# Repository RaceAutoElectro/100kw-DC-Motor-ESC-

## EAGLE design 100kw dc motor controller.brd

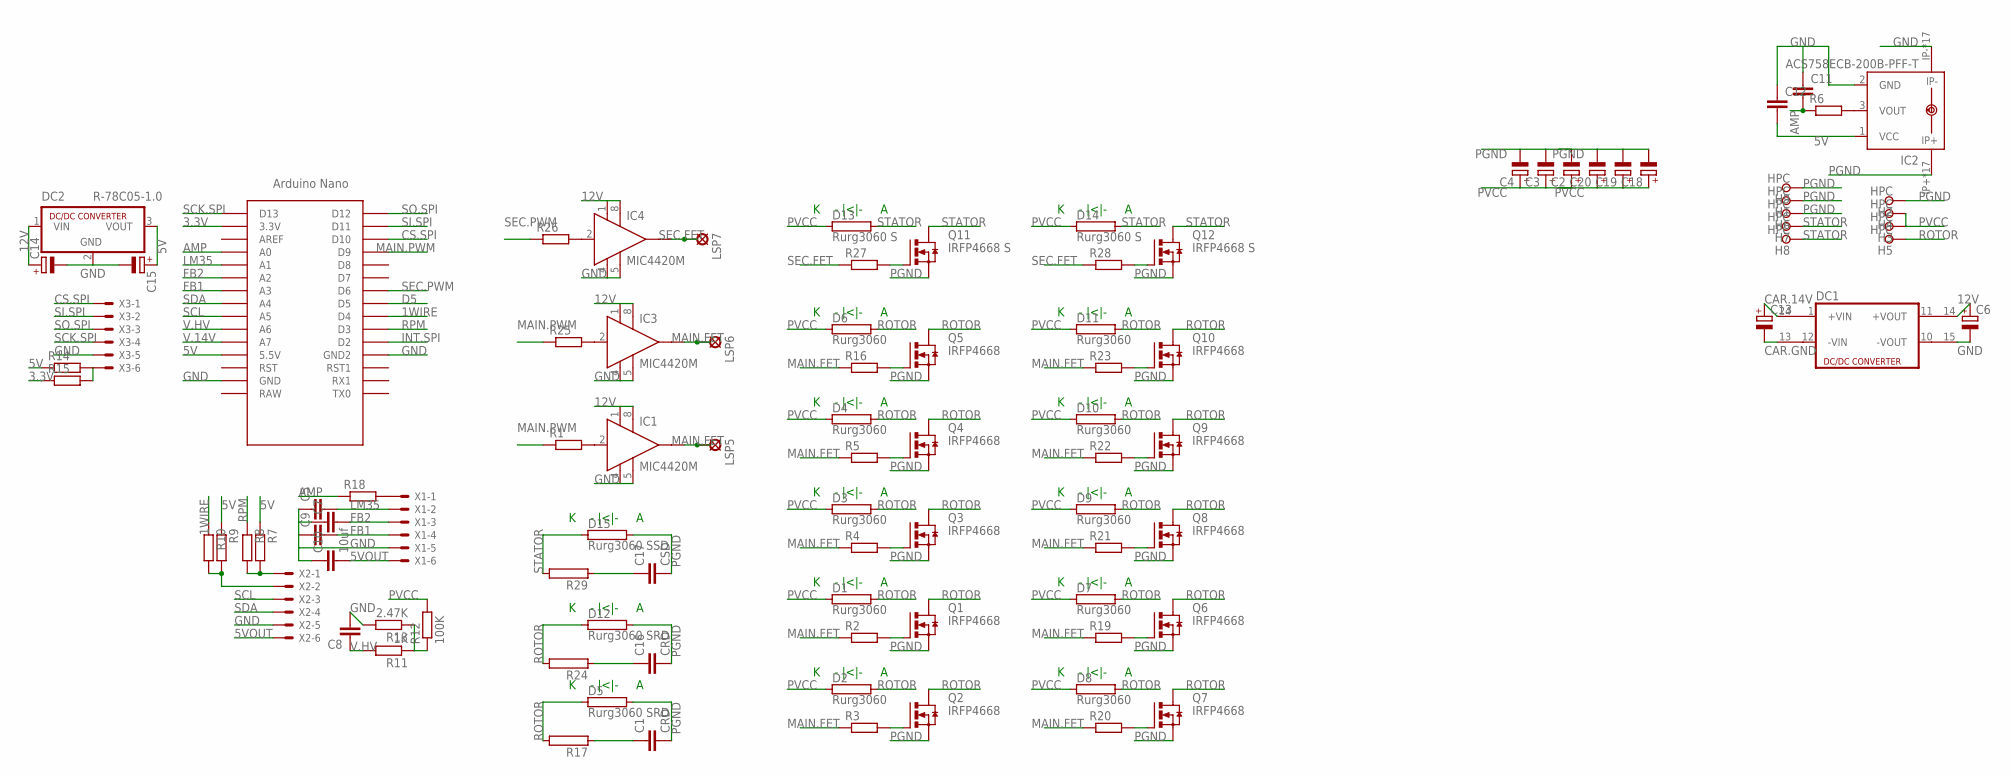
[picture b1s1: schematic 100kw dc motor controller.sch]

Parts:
C1, C16: CRD; C37.5B20
C2, C3, C4, C18, C19, C20: CPOL-EUE10-35; EB35D
C5, C7, C8, C9, C11, C12: C-EUC1206; C1206
C6, C13: CPOL-EUE3.5-10; E3,5-10
C10: 10uf; C1812
C14, C15: CPOL-EUD/7343-31W; D/7343-31W
C17: CSD; C37.5B20
D1, D2, D3, D4, D6, D7, D8, D9, D10, D11: Rurg3060; TO-247-2H
D5, D12: Rurg3060 SRD; TO-247-2V
D13, D14: Rurg3060 S; TO-247-2H
D15: Rurg3060 SSD; TO-247-2V
DC1: DCW1U; DCW
DC2: R-78C05-1.0; SIP3
H1, H2, H3, H4, H5, H6, H7, H8, H9: HPC; PAD_0.2500
IC1, IC3, IC4: MIC4420M; SO-08
IC2: ACS758ECB-200B-PFF-T; CB-PFF
LSP5, LSP6, LSP7: LSP11
Q1, Q2, Q3, Q4, Q5, Q6, Q7, Q8, Q9, Q10: IRFP4668; TO247BH
Q11, Q12: IRFP4668 S; TO247BH
R1, R6, R7, R8, R9, R10, R14, R15, R18, R25, R26: R-EU_R1206; R1206
R2, R3, R4, R5, R16, R19, R20, R21, R22, R23, R27, R28: R-EU_M5923; M5923
R11: 1K; R1206
R12: 100K; R1206
R13: 2.47K; R1206
R17, R24, R29: RKH208-8R; KH208R-8
U$1: NANO
X1, X2, X3: 22-23-2061

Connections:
1WIRE: R10.1, U$1.D4
3.3V: R15.1, U$1.3.3V
5V: C12.2, C15.+, DC2.3 (VOUT), IC2.1 (VCC), R7.1, R9.1, R14.1, U$1.5V (5.5V)
5VOUT: C10.2, X1.6, X2.6
12V: C6.+, C14.+, DC1.14 (+VOUT1), DC2.1 (VIN), IC1.1 (VS), IC1.8 (VS1), IC3.1 (VS), IC3.8 (VS1), IC4.1 (VS), IC4.8 (VS1)
AMP: C11.2, R6.1, R18.1, U$1.A0
CAR.14V: C13.+, DC1.24 (+VIN1)
CAR.GND: C13.-, DC1.13 (-VIN1)
CS.SPI: U$1.D10, X3.1
D5: U$1.D5
FB1: C9.2, U$1.A3, X1.4
FB2: C7.2, U$1.A2, X1.3
GND: C5.1, C6.-, C7.1, C8.2, C9.1, C10.1, C11.1, C12.1, C14.-, C15.-, DC1.15 (-VOUT1), DC2.2 (GND), IC1.4 (GND), IC1.5 (GND1), IC2.2 (GND), IC2.IP-, IC2.IP-@2 (IP-), IC2.IP-@3 (IP-), IC2.IP-@4 (IP-), IC2.IP-@5 (IP-), IC2.IP-@6 (IP-), IC2.IP-@7 (IP-), IC2.IP-@8 (IP-), IC2.IP-@9 (IP-), IC2.IP-@10 (IP-), IC2.IP-@11 (IP-), IC2.IP-@12 (IP-), IC2.IP-@13 (IP-), IC2.IP-@14 (IP-), IC2.IP-@15 (IP-), IC2.IP-@16 (IP-), IC2.IP-@17 (IP-), IC3.4 (GND), IC3.5 (GND1), IC4.4 (GND), IC4.5 (GND1), R13.2, U$1.GND, U$1.GND1 (GND2), X1.5, X2.5, X3.5
INT.SPI: U$1.D2
LM35: C5.2, U$1.A1, X1.2
MAIN.FET: IC1.6 (OUT), IC3.6 (OUT), LSP5.MP, LSP6.MP, R2.1, R3.1, R4.1, R5.1, R16.1, R19.1, R20.1, R21.1, R22.1, R23.1
MAIN.PWM: R1.1, R25.1, U$1.D9
unnamed: IC1.2 (IN), R1.2
unnamed: Q1.G, R2.2
unnamed: Q2.G, R3.2
unnamed: Q3.G, R4.2
unnamed: Q4.G, R5.2
unnamed: IC2.3 (VOUT), R6.2
unnamed: R9.2, R10.2, X2.2
unnamed: R7.2, R8.2, X2.1
unnamed: R14.2, R15.2, X3.6
unnamed: Q5.G, R16.2
unnamed: C1.1, R17.1
unnamed: R18.2, X1.1
unnamed: R11.1, R12.1, R13.1
unnamed: Q6.G, R19.2
unnamed: Q7.G, R20.2
unnamed: Q8.G, R21.2
unnamed: Q9.G, R22.2
unnamed: Q10.G, R23.2
unnamed: C16.1, R24.1
unnamed: IC3.2 (IN), R25.2
unnamed: IC4.2 (IN), R26.2
unnamed: Q11.G, R27.2
unnamed: Q12.G, R28.2
unnamed: C17.1, R29.1
PGND: C1.2, C2.-, C3.-, C4.-, C16.2, C17.2, C18.-, C19.-, C20.-, D5.2, D12.2, D15.2, H1.1, H2.1, H6.1, H9.1, IC2.IP+, IC2.IP+@2 (IP+), IC2.IP+@3 (IP+), IC2.IP+@4 (IP+), IC2.IP+@5 (IP+), IC2.IP+@6 (IP+), IC2.IP+@7 (IP+), IC2.IP+@8 (IP+), IC2.IP+@9 (IP+), IC2.IP+@10 (IP+), IC2.IP+@11 (IP+), IC2.IP+@12 (IP+), IC2.IP+@13 (IP+), IC2.IP+@14 (IP+), IC2.IP+@15 (IP+), IC2.IP+@16 (IP+), IC2.IP+@17 (IP+), Q1.S, Q2.S, Q3.S, Q4.S, Q5.S, Q6.S, Q7.S, Q8.S, Q9.S, Q10.S, Q11.S, Q12.S
PVCC: C2.+, C3.+, C4.+, C18.+, C19.+, C20.+, D1.1, D2.1, D3.1, D4.1, D6.1, D7.1, D8.1, D9.1, D10.1, D11.1, D13.1, D14.1, H3.1, H4.1, R12.2
ROTOR: D1.2, D2.2, D3.2, D4.2, D5.1, D6.2, D7.2, D8.2, D9.2, D10.2, D11.2, D12.1, H5.1, Q1.D, Q2.D, Q3.D, Q4.D, Q5.D, Q6.D, Q7.D, Q8.D, Q9.D, Q10.D, R17.2, R24.2
RPM: R8.1, U$1.D3
SCK.SPI: U$1.D13, X3.4
SCL: U$1.A5, X2.3
SDA: U$1.A4, X2.4
SEC.FET: IC4.6 (OUT), LSP7.MP, R27.1, R28.1
SEC.PWM: R26.1, U$1.D6
SI.SPI: U$1.D11, X3.2
SO.SPI: U$1.D12, X3.3
STATOR: D13.2, D14.2, D15.1, H7.1, H8.1, Q11.D, Q12.D, R29.2
V.14V: U$1.A7
V.HV: C8.1, R11.2, U$1.A6

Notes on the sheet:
K - |<|- A

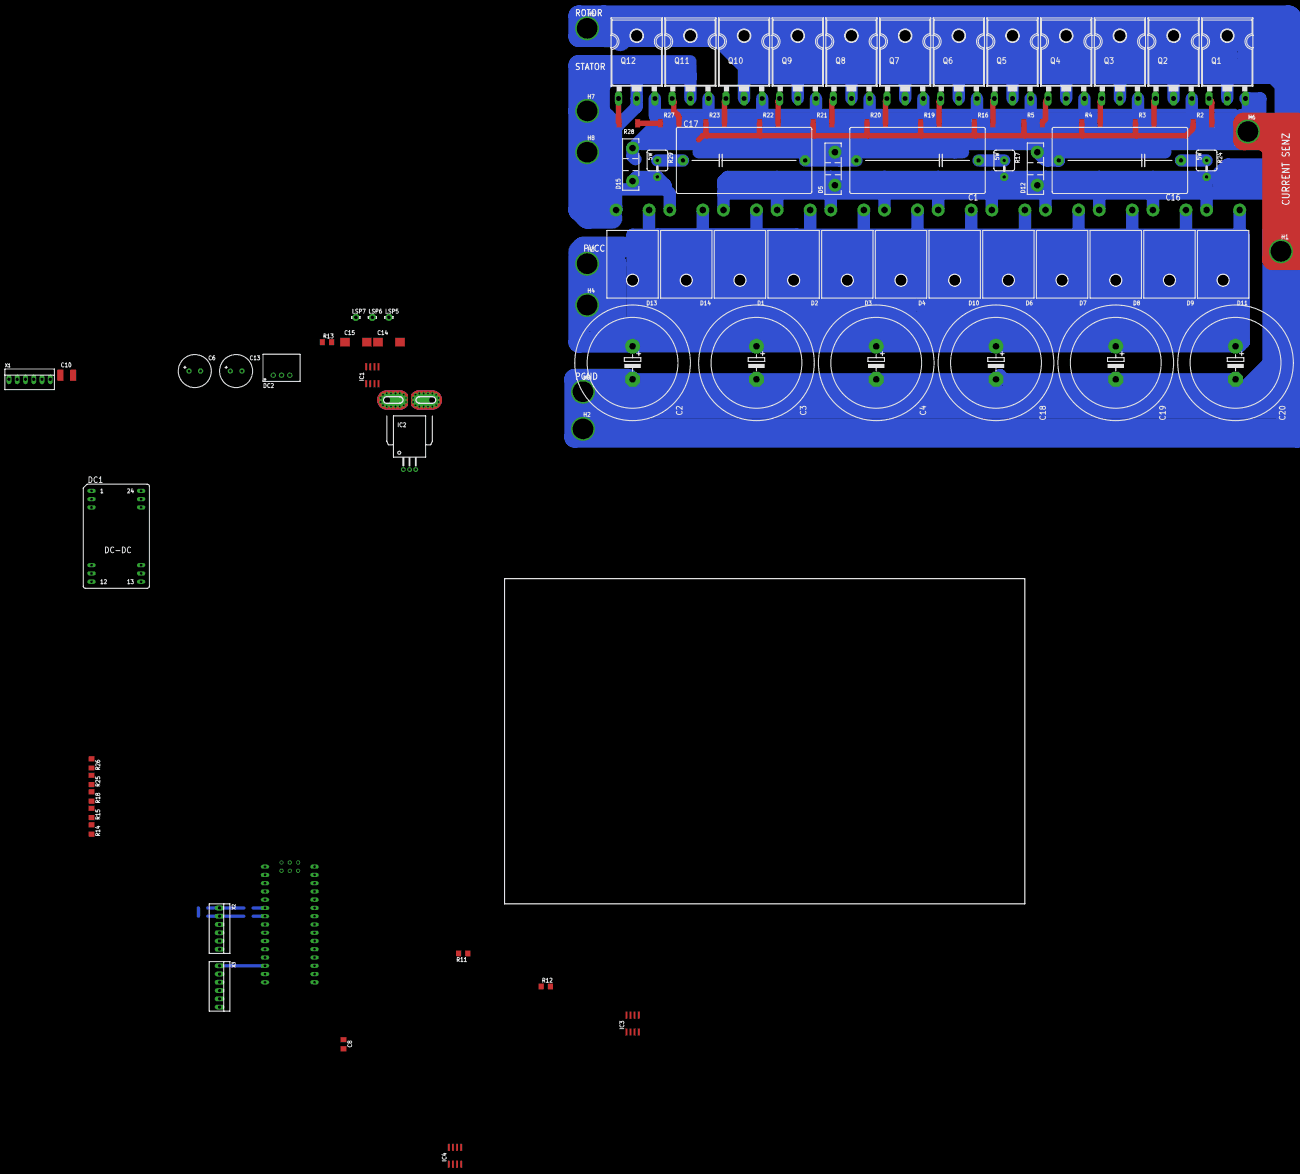
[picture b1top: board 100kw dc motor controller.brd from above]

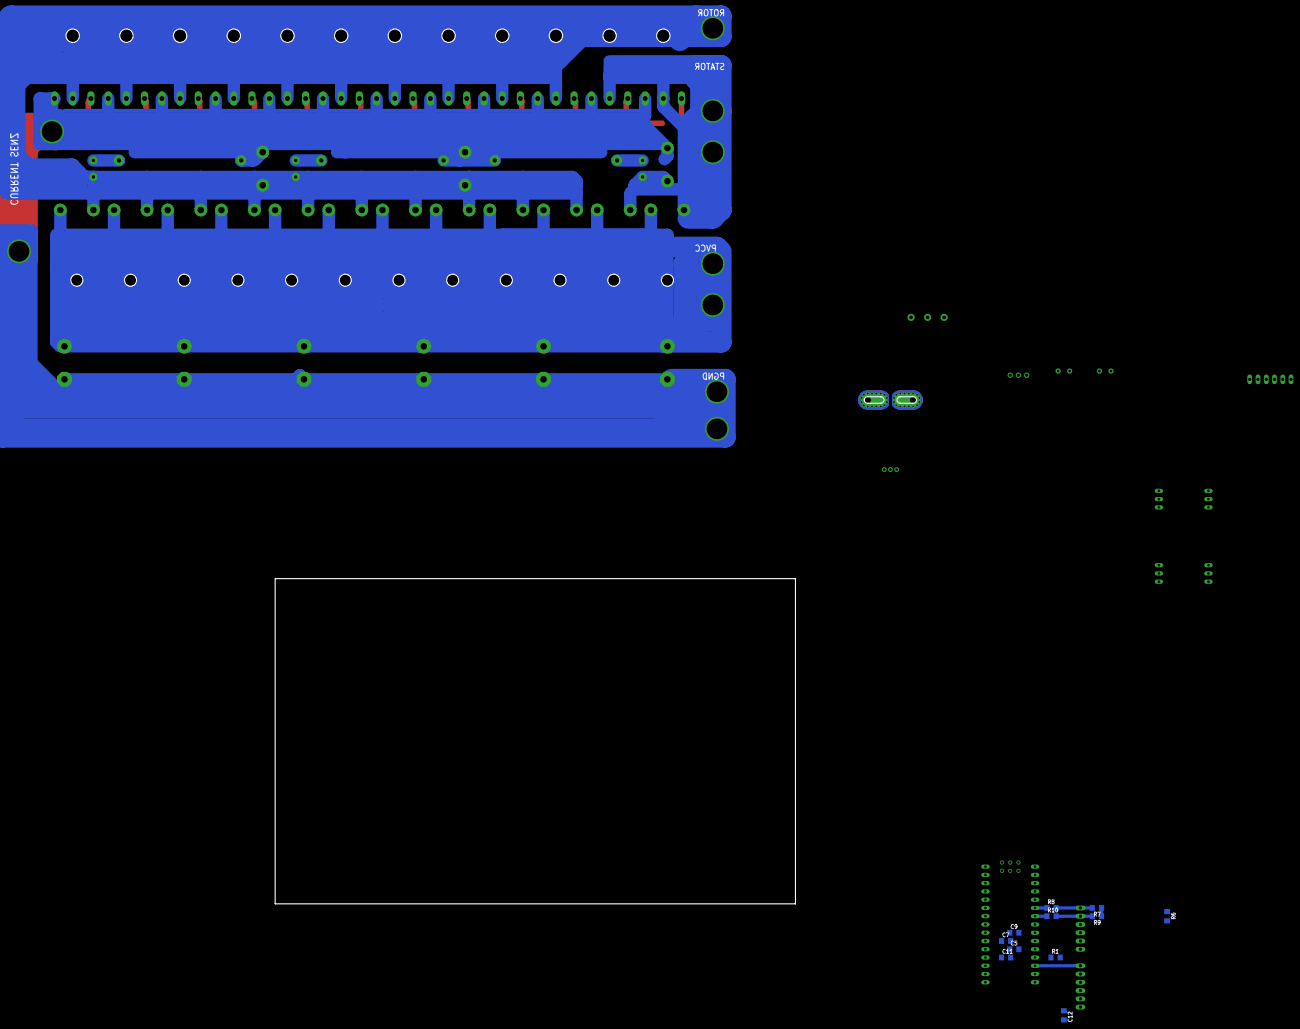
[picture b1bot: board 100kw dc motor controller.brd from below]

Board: 2 copper layers, 98 parts (11 on the bottom side), 52 nets.

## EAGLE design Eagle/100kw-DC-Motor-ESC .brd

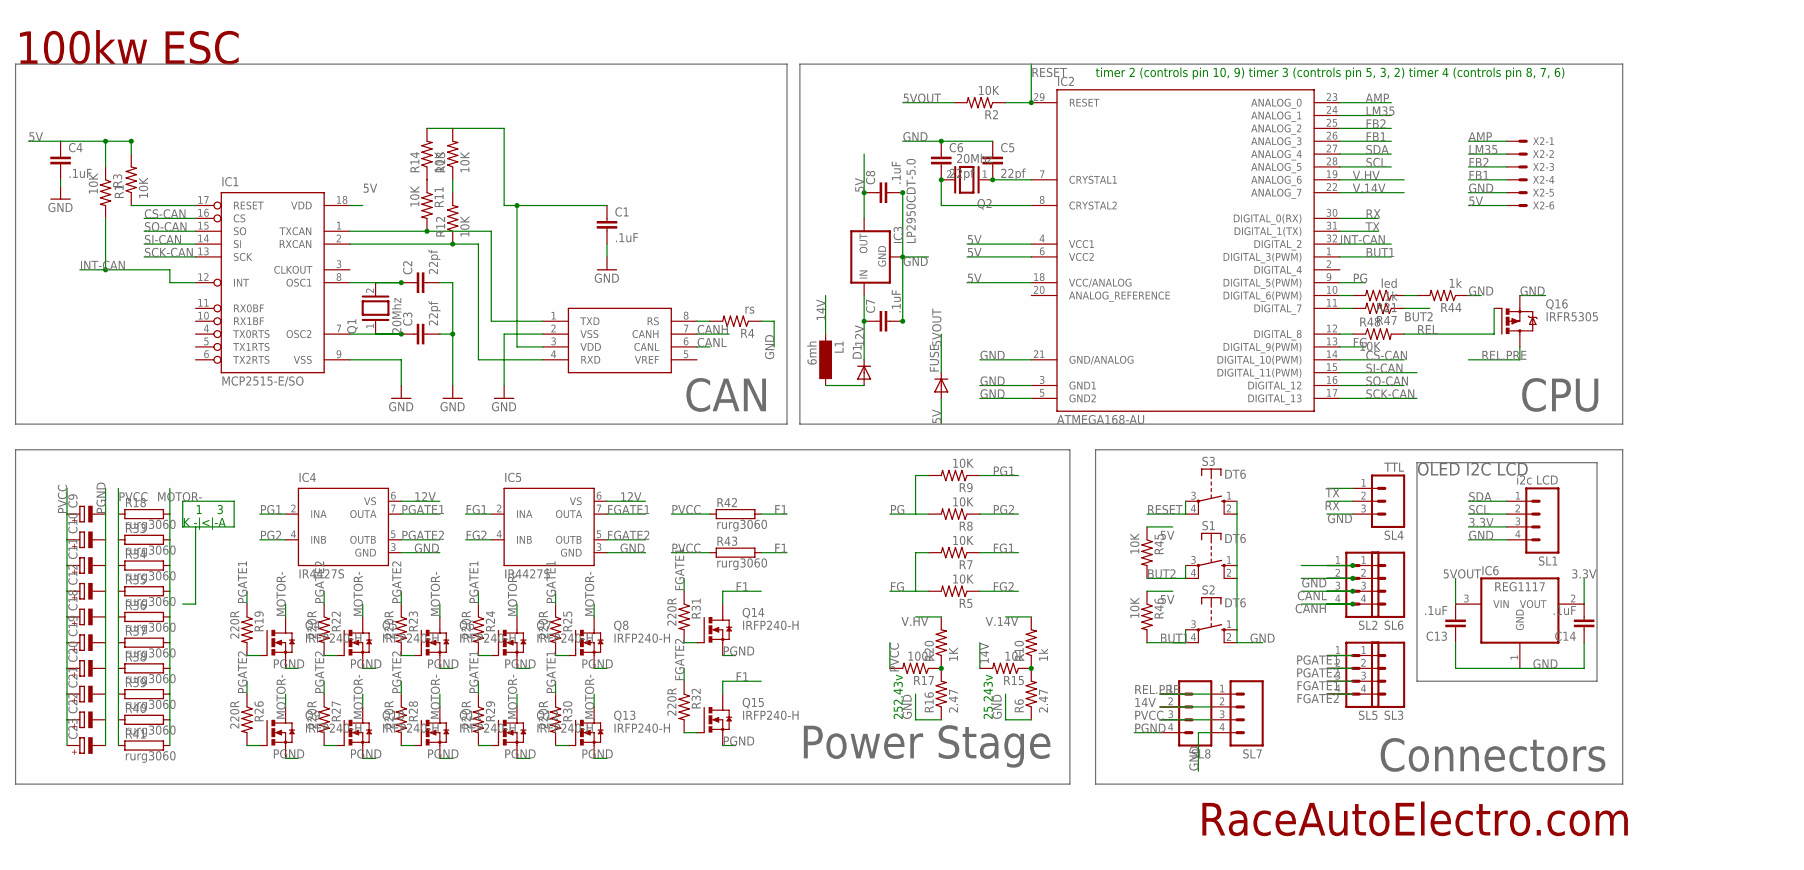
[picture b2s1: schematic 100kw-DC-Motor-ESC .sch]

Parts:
C1: .1uF; 0805
C2, C3, C5, C6: 22pf; 0805
C4, C7, C8, C13, C14: .1uF; 1210
C9, C10, C11, C12, C18, C19, C20, C21, C22, C23: CPOL-EUE10-35; EB35D
D1: DIODE-DO-214AC; DO-214AC
FUSE: DIODE-DO-214AC; DO-214AC
IC1: MCP2515-E/SO; SO18L
IC2: ATMEGA168-AU; TQFP32-08
IC3: LP2950CDT-5.0; DPACK
IC4, IC5: IR4427S; SO08
IC6: REG1117; SOT223
L1: 6mh; MS85
Q1, Q2: 20Mhz; QS
Q4, Q5, Q6, Q7, Q8, Q9, Q10, Q11, Q12, Q13, Q14, Q15: IRFP240-H; TO247BH
Q16: IRFR5305; D-PAK_TO252AA
R1, R3, R5, R7, R8, R9, R11, R12, R13, R14, R45, R46, R48: 10K; 0805
R2: 10K; 1206
R4: rs; 0805
R6, R16: 2.47; 0805
R10, R44, R47: 1k; 0805
R15: 10k; 0805
R17: 100k; 0805
R18, R33, R34, R35, R36, R37, R38, R39, R40, R41, R42, R43: rurg3060; TO-247-2H
R19, R22, R23, R24, R25, R26, R27, R28, R29, R30, R31, R32: 220R; 0805
R20: 1K; 0805
R21: led; 1206
S1, S2, S3: DT6
SL1: i2c LCD; 04P
SL2, SL3, SL5, SL6, SL7, SL8: M04; 04P
SL4: TTL; 03P
U1: MCP2551; SO08
X2: 22-23-2061

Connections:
3.3V: C14.2, IC6.2 (VOUT), SL1.3
5V: C1.1, C4.1, C8.1, FUSE.A, IC1.18 (VDD), IC2.4 (VCC1), IC2.6 (VCC2), IC2.18 (VCC/ANALOG), IC3.3 (OUT), R1.2, R3.1, R13.2, R14.2, R45.1, R46.1, U1.3 (VDD), X2.6
5VOUT: C13.2, FUSE.C, IC6.3 (VIN), R2.2
12V: C7.1, D1.C, IC3.1 (IN), IC4.6 (VS), IC5.6 (VS)
14V: L1.1, R15.2, SL7.2, SL8.2
AMP: IC2.23 (ANALOG_0), X2.1
BUT1: IC2.1 (DIGITAL_3(PWM)), R46.2, S2.3, S2.4
BUT2: R45.2, R47.1, S1.3, S1.4
BUT2R: IC2.11 (DIGITAL_7), R47.2
CANH: SL2.4, SL6.4, U1.7 (CANH)
CANL: SL2.3, SL6.3, U1.6 (CANL)
CS-CAN: IC1.16 (CS), IC2.14 (DIGITAL_10(PWM))
F1: Q14.D, Q15.D, R42.2, R43.2
FB1: IC2.26 (ANALOG_3), X2.4
FB2: IC2.25 (ANALOG_2), X2.3
FG: IC2.13 (DIGITAL_9(PWM)), R5.2, R7.2
FG1: IC5.2 (INA), R7.1
FG2: IC5.4 (INB), R5.1
FGATE1: IC5.7 (OUTA), R31.1, SL3.3, SL5.3
FGATE2: IC5.5 (OUTB), R32.1, SL3.4, SL5.4
GND: C1.2, C2.2, C3.2, C4.2, C5.1, C6.1, C7.2, C8.2, C13.1, C14.1, IC1.9 (VSS), IC2.3 (GND1), IC2.5 (GND2), IC2.21 (GND/ANALOG), IC3.4 (GND), IC4.3 (GND), IC5.3 (GND), IC6.1 (GND), Q16.3 (S), R4.1, R6.1, R16.1, R44.1, S1.1 (S), S1.2 (S), S2.1 (S), S2.2 (S), S3.1 (S), S3.2 (S), SL1.4, SL2.2, SL4.3, SL6.2, SL7.4, U1.2 (VSS), X2.5
INT-CAN: IC1.12 (INT), IC2.32 (DIGITAL_2), R3.2
LM35: IC2.24 (ANALOG_1), X2.2
MOTOR-: Q4.D, Q5.D, Q6.D, Q7.D, Q8.D, Q9.D, Q10.D, Q11.D, Q12.D, Q13.D, R18.2, R33.2, R34.2, R35.2, R36.2, R37.2, R38.2, R39.2, R40.2, R41.2
unnamed: R4.2, U1.8 (RS)
unnamed: IC1.1 (TXCAN), R11.2, U1.1 (TXD)
unnamed: IC1.2 (RXCAN), R12.1, U1.4 (RXD)
unnamed: C2.1, IC1.8 (OSC1), Q1.2
unnamed: C3.1, IC1.7 (OSC2), Q1.1
unnamed: C5.2, IC2.7 (CRYSTAL1), Q2.1
unnamed: Q4.G, R19.2
unnamed: IC1.17 (RESET), R1.1
unnamed: C6.2, IC2.8 (CRYSTAL2), Q2.2
unnamed: IC2.12 (DIGITAL_8), R48.1
unnamed: D1.A, L1.2
unnamed: R12.2, R13.1
unnamed: Q5.G, R22.2
unnamed: R11.1, R14.1
unnamed: Q6.G, R23.2
unnamed: Q7.G, R24.2
unnamed: Q8.G, R25.2
unnamed: Q9.G, R26.2
unnamed: Q10.G, R27.2
unnamed: Q11.G, R28.2
unnamed: Q12.G, R29.2
unnamed: Q13.G, R30.2
unnamed: Q14.G, R31.2
unnamed: Q15.G, R32.2
unnamed: SL2.1, SL6.1
unnamed: R6.2, R10.1, R15.1
unnamed: IC2.10 (DIGITAL_6(PWM)), R21.2
unnamed: R21.1, R44.2
unnamed: R16.2, R17.1, R20.1
PG: IC2.9 (DIGITAL_5(PWM)), R8.2, R9.2
PG1: IC4.2 (INA), R9.1
PG2: IC4.4 (INB), R8.1
PGATE1: IC4.7 (OUTA), R19.1, R24.1, R25.1, R29.1, R30.1, SL3.1, SL5.1
PGATE2: IC4.5 (OUTB), R22.1, R23.1, R26.1, R27.1, R28.1, SL3.2, SL5.2
PGND: C9.-, C10.-, C11.-, C12.-, C18.-, C19.-, C20.-, C21.-, C22.-, C23.-, Q4.S, Q5.S, Q6.S, Q7.S, Q8.S, Q9.S, Q10.S, Q11.S, Q12.S, Q13.S, Q14.S, Q15.S, SL8.4
PVCC: C9.+, C10.+, C11.+, C12.+, C18.+, C19.+, C20.+, C21.+, C22.+, C23.+, R17.2, R18.1, R33.1, R34.1, R35.1, R36.1, R37.1, R38.1, R39.1, R40.1, R41.1, R42.1, R43.1, SL7.3, SL8.3
REL: Q16.1 (G), R48.2
REL.PRE: Q16.4 (D), SL7.1, SL8.1
RESET: IC2.29 (RESET), R2.1, S3.3, S3.4
RX: IC2.30 (DIGITAL_0(RX)), SL4.2
SCK-CAN: IC1.13 (SCK), IC2.17 (DIGITAL_13)
SCL: IC2.28 (ANALOG_5), SL1.2
SDA: IC2.27 (ANALOG_4), SL1.1
SI-CAN: IC1.14 (SI), IC2.15 (DIGITAL_11(PWM))
SO-CAN: IC1.15 (SO), IC2.16 (DIGITAL_12)
TX: IC2.31 (DIGITAL_1(TX)), SL4.1
V.14V: IC2.22 (ANALOG_7), R10.2
V.HV: IC2.19 (ANALOG_6), R20.2

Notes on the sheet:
CAN
Power Stage
Connectors
RaceAutoElectro.com
100kw ESC
CPU
K -|<|-A
1 3
OLED I2C LCD
25.243v
252.43v
timer 2 (controls pin 10, 9) timer 3 (controls pin 5, 3, 2) timer 4 (controls pin 8, 7, 6)

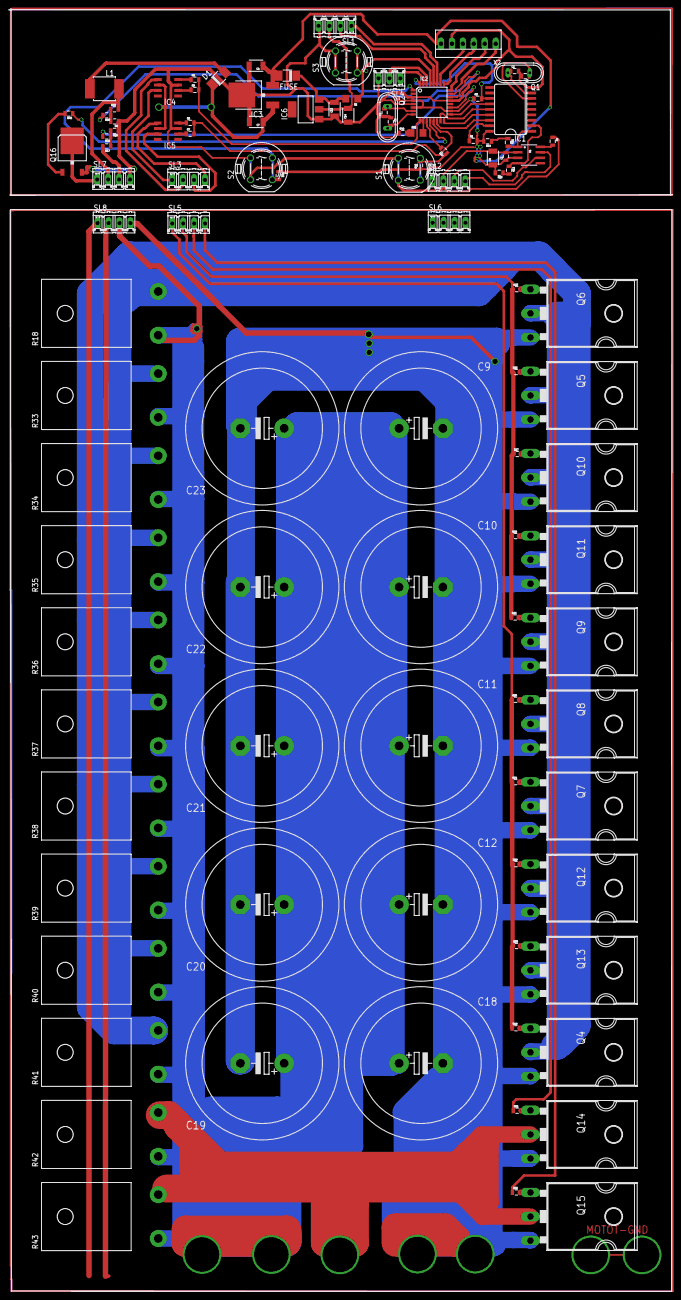
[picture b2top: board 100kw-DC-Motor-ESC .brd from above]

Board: 2 copper layers, 154.1 x 297.6 mm, 105 parts (0 on the bottom side), 72 nets.

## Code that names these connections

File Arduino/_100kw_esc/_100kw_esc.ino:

#define SERIAL_ENABLED 1
#define LCD_ENABLED 1
#include <Wire.h>
#if LCD_ENABLED
#include <LiquidCrystal_I2C.h>
// Set the LCD address to 0x27 for a 16 chars and 2 line display
LiquidCrystal_I2C lcd(0x27, 20, 4, LCD_5x8DOTS);
#endif
// These defines won't change.  They're used to give names to the pins used:


#define ROTOR_CURRENT_PIN A0                // A1302 hall senzor Rotor
#define TEMP_PIN A1                   // pinA1 - lm35 temp senzor
#define FB2_PIN A3                    // FB2     947 - 562   (Bosch)
#define FB1_PIN A2                    // FB1     157 - 940   (Bosch)
#define HV_PIN A6                     // volt-HV 100k & 2.2k
#define STATOR_CURRENT_PIN A7              // A1302 hall senzor Stator
#define MAINREL 8                     // MainRelay
#define ROTOR_PWM_PIN 9               // Rotor PWM 
#define STATOR_PWM_PIN 6              // Stator PWM ( field armature )

#define MIN_STATOR_CURRENT 1
#define MAX_ROTOR_CURRENT 100                   // Max AMP - Rotor
#define MAX_STATOR_CURRENT 5                   // Max AMP - Stator
#define ROTOR_OVERCURRENT 500
#define STATOR_OVERCURRENT 100
#define Kp 1                          // Motor Parameters (Rotor)
//#define TARGET_MULTIPLIER_S 4         // Motor Parameters (Stator)
#define Kp_S 0.2                      // Motor Parameters (Stator)
#define BATTERY_LOW 120
#define POWERSTAGE_DOWN 80
unsigned short int MainFB = 0;                       // MainFB ( TPS1 )
unsigned short int SecFB = 0;                        // SecFB ( TPS2 )
unsigned short int HiVoltage = 0;                  // Hi  Voltage 0-220v
byte rotorPWM = 0;                    // rotorPWM for Rotor
byte statorPWM = 0;                       // statorPWM for Stator
byte temperature = 0;                    //  lm35 -temperature sensor
signed int rotorCurrent = 0, rotorTargetCurrent = 0;         //  A1302 hall senzor
signed int statorCurrent = 0, statorTargetCurrent = 0;       //  A1302 hall senzor stator
unsigned int consumedPower = 0;                //
signed int baselineRotorCurrent = 0;                  // Initial AMP read  (Rotor)
unsigned int baselineStatorCurrent = 0;                 // Initial AMPs read  (Stator)
struct {
  byte rotorOverCurrent: 1;
  byte statorOverCurrent: 1;
  byte statorUnderCurrent: 1;
  byte batteryLow: 1;
  byte powerStageDown: 1;
  byte overTemperature: 1;
} status;

unsigned long milliseconds;           // Delay with milis + task_10ms
void task_10mS () {
  unsigned long localTime = millis();
  if (localTime - milliseconds > 10) {
    milliseconds = localTime;
    checkConditions();
#if SERIAL_ENABLED                    // Serial 
    // print the results to the serial monitor:
    //  Serial.print("MainFB = ");
    //  Serial.print(MainFB);
    //Serial.print("\t rotorPWM = ");
    Serial.print("\t");
    Serial.print(HiVoltage);
    //  Serial.print("\t temp = ");
    //  Serial.print(tempValue);
    //  Serial.print("\t rotorPWM = ");
    //  Serial.print(rotorPWM);
    //  Serial.print("\t statorPWM = ");
    //  Serial.print(statorPWM);
    Serial.println( );
#endif

#if LCD_ENABLED                       // Lcd
    //lcd.clear();
    lcd.setCursor(0, 0);
    lcd.print((float)(HiVoltage));
    lcd.print("V");
    lcd.setCursor(9, 0);
    lcd.print(rotorCurrent);
    lcd.print("RA");
    //lcd.setCursor(0, 1);
    //lcd.print(temperature);
    //lcd.print("C");
    lcd.setCursor(9, 1);
    lcd.print((float)(statorCurrent / 10.0f));
    lcd.print("SA");
    lcd.setCursor(0, 2);
    lcd.print(consumedPower);
    lcd.print("W");
#endif
    // wait 2 milliseconds before the next loop
    // for the analog-to-digital converter to settle
    // after the last reading:
    //delay(200);
  }
}
void checkConditions() {
  if (statorCurrent < MIN_STATOR_CURRENT) {
    digitalWrite(MAINREL, LOW);
#if LCD_ENABLED
    lcd.setCursor(0, 3);
    lcd.print("Stator down");
    status.statorUnderCurrent = 1;
#endif
  }
  if (HiVoltage < BATTERY_LOW) {
    digitalWrite(MAINREL, LOW);
#if LCD_ENABLED
    lcd.setCursor(0, 3);
    lcd.print("Batt low    ");
    status.batteryLow = 1;
#endif
  }
  if (HiVoltage < POWERSTAGE_DOWN) {
    digitalWrite(MAINREL, LOW);
#if LCD_ENABLED
    lcd.setCursor(0, 3);
    lcd.print("PStage down  ");
    status.powerStageDown = 1;
#endif
  }
  if (rotorCurrent > ROTOR_OVERCURRENT) {
    digitalWrite(MAINREL, LOW);
#if LCD_ENABLED
    lcd.setCursor(0, 3);
    lcd.print("Rotor short");
    status.rotorOverCurrent = 1;
#endif
  }
  if (statorCurrent > STATOR_OVERCURRENT) {
    digitalWrite(MAINREL, LOW);
#if LCD_ENABLED
    lcd.setCursor(0, 3);
    lcd.print("Stator short");
    status.statorOverCurrent = 1;
#endif
  }

}

void setup() {
  status.rotorOverCurrent = 0;
  status.statorOverCurrent = 0;
  status.statorUnderCurrent = 0;
  status.batteryLow = 0;
  status.powerStageDown = 0;
  status.overTemperature = 0;
  pinMode(MAINREL, OUTPUT);
  pinMode(STATOR_PWM_PIN, OUTPUT);
  pinMode(ROTOR_PWM_PIN, OUTPUT);
  digitalWrite(STATOR_PWM_PIN, 0); //Stator
  digitalWrite(ROTOR_PWM_PIN, 0);  //Rotor
  //digitalWrite(MAINREL, HIGH); //Stator
  for (char i = 0; i < 30; i++) {
    baselineRotorCurrent += analogRead(ROTOR_CURRENT_PIN);
    baselineStatorCurrent += analogRead(STATOR_CURRENT_PIN); //Stator
  }
  baselineRotorCurrent = baselineRotorCurrent / 30;  //Rotor
  baselineStatorCurrent = baselineStatorCurrent / 30; //Stator
  delay(200);

#if SERIAL_ENABLED
  // initialize serial communications at 115200 bps:
  Serial.begin(115200);
#endif

#if LCD_ENABLED
  // initialize the LCD
  lcd.begin();
  // Turn on the blacklight and print a message.
  lcd.backlight();
#endif
  //if (HiVoltage > POWERSTAGE_DOWN)
  digitalWrite(MAINREL, HIGH);
  statorPWM = 20;
  analogWrite(STATOR_PWM_PIN, statorPWM);
  delay(3000);
}

void loop() {
  // read the analog in value:
  temperature = (500 * analogRead(A1)) / 1024;
  rotorCurrent = 0;
  statorCurrent = 0;  //Stator
  HiVoltage = 0;

  for (char i = 0; i < 30; i++) {
    rotorCurrent += analogRead(ROTOR_CURRENT_PIN);
    HiVoltage += analogRead(HV_PIN);
    statorCurrent += analogRead(STATOR_CURRENT_PIN); //Stator
  }

  //rotorCurrent = (rotorCurrent / 30 + 512) / 2 - baselineRotorCurrent;
  rotorCurrent = (rotorCurrent / 30) - baselineRotorCurrent;
  statorCurrent = (statorCurrent / 30) - baselineStatorCurrent;
  //statorCurrent = ( (statorCurrent / 30 + 518) / 2 - baselineStatorCurrent) * 2.1 ; //Stator
  HiVoltage = HiVoltage / 192;
  consumedPower = (HiVoltage * (rotorCurrent + statorCurrent)) / 100;     // Power for Stator + Rotor
  //MainFB = analogRead(FB1_PIN );
  //MainFB = constrain(MainFB, 154, 940);
  MainFB =  analogRead(FB1_PIN );
  MainFB = constrain(MainFB, 310, 760);
  // map it to the range of the analog out:
  //mai intai te uiti ca iti vine MAINFB si SECFB ca limite si bagi limitele in map
  //rotorPWM = map(MainFB, 154, 940, 0, 12); //limita laPWM 4.7%
  rotorTargetCurrent = map(MainFB, 310, 770, 0, MAX_ROTOR_CURRENT); //limita la MAX_ROTOR_CURRENT Rotor
  //TargetAMPS = map(MainFB, 310, 770, 0, MAX_STATOR_CURRENT*TARGET_MULTIPLIER_S);   //limita la MAX_ROTOR_CURRENT Stator
  //statorTargetCurrent = MAX_STATOR_CURRENT;
  rotorPWM = (rotorTargetCurrent - rotorCurrent) * Kp;
  //statorPWM = (statorTargetCurrent - statorCurrent) * Kp_S;
  // change the analog out value:
  analogWrite(ROTOR_PWM_PIN, 0);
  //analogWrite(ROTOR_PWM_PIN, rotorPWM);
  analogWrite(STATOR_PWM_PIN, statorPWM);
  task_10mS();
}

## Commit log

2016-03-28 :lollipop: Added .gitattributes & .gitignore files
2016-03-29 v1.1
2016-04-20 Update _100kw_esc.ino
    added i2c lcd
2016-05-31 v0.5
2016-05-31 new code
2016-07-02 Create Arduino_100kw_esc.field
    added curent senzor for stator on A7 , Power on lcd
